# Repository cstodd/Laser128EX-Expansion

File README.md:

# Laser 128EX 1 MB RAM + Clock Expansion

A replacement memory-expansion card for the **Laser 128EX** (and, by the shared connector, the New Laser 128):
**1 MB of battery-backed SRAM** in place of the stock card's 32 DRAMs, plus a **real-time clock** that gives
ProDOS 8 file dates and the time. It plugs into the Laser's internal J13 expansion connector, uses the Laser's
own expansion-RAM interface (`$C0D0–$C0D3`), so the built-in `/RAM5` RAM disk, the firmware and the diagnostics
work unchanged, and the RAM disk survives power-off.

It continues Renée Harke's earlier CPLD + SRAM card for the Laser, which was never finished.

## Status (Nov 2026)
- **Rev 0.2 board: ready to order.** Routed 2-layer, 100 × 90 mm, DRC clean, Gerbers in `hardware/rev02/fab/`.
- **CPLD logic: fitted** (ATF1504AS, 40/64 macrocells); passes its testbench as RTL, fitted equations and decoded
  fuses. The testbench uses strobe timing measured with a scope on a real 128EX (`cpld/rev02/README.md`).
- **ProDOS clock driver: done** (fits in ProDOS's 125-byte clock slot, never disables interrupts), with
  CLOCK.SYSTEM, SET.CLOCK and CARD.TEST on `software/rev02/dist/LASERCLOCK2.po`; emulator-tested.
- **Not yet built.** Next: order boards, assemble, bring up (`docs/bring-up.md`).

## How it works, briefly
The Laser's gate arrays already hold the slinky address register and drive the card with multiplexed DRAM
signals. A CPLD turns those into SRAM addresses and strobes (latching row and column the way DRAM would) for two
512K×8 SRAMs, whose supply and chip enable come from a MAX693A so they keep their contents on a CR2032. J13 has
no spare pins, so the clock (a DS3234 on SPI) is reached **through the RAM data port**: an 8-byte unlock key
written to `$C0D3` switches the CPLD into RTC mode for one transfer. Details: `docs/design-notes.md`.

## Repository
New here (or a fresh Claude session)? Start with `progress.md`, `changelog.md`, `architecture.md` and
`building.md`; `CLAUDE.md` has the working rules.

| Path | What |
|---|---|
| `hardware/rev02/` | **Current board**: KiCad 10 schematic + PCB, `fab/` (Gerbers, drill, BOM, placement), renders, README |
| `cpld/rev02/` | CPLD Verilog, testbench (DS3234 model, measured Laser timing), fitter flow and `.jed` |
| `software/rev02/` | ProDOS clock driver, CLOCK.SYSTEM, SET.CLOCK, CARD.TEST, disk image, emulator tests |
| `docs/ordering.md` | What to order (PCB settings, parts list); open checks in `hardware/rev02/todo.md` |
| `docs/bring-up.md` | Assembly order, programming the CPLD, first power-up and tests |
| `docs/scope-tests.md` | How the J13 timing was measured, with monitor test loops |
| `docs/design-notes.md` | Design decisions and history |
| `docs/laser-expansion-interface.md` | The Laser's expansion RAM interface (from the Technical Reference Manual) |
| `docs/sourcing.md`, `docs/mechanical.md` | Part availability; board outline and clearances |
| `hardware/rev01/`, `cpld/rev01/`, `software/rev01/` | Rev 0.1 (DS3231 on I²C): superseded, kept for reference |
| `tools/` | Scripts that generated / edited the boards and fab outputs |

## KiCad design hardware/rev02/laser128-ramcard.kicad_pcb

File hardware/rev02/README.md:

# Hardware (KiCad) — rev 0.2

Rev 0.2 replaces rev 0.1's DS3231M (I²C, bit-banged through the CPLD) with a **DS3234SN#** (SPI) so the
ProDOS clock driver fits entirely in ProDOS's 125-byte clock slot and never disables interrupts
(`software/rev02`, `cpld/rev02`, `docs/design-notes.md` §10). Everything else (RAM, CPLD, J1, outline,
holes) is unchanged from rev 0.1 (`hardware/rev01`).

Status (rev 0.2): **fully routed, 2 layers, 100 × 90 mm, KiCad 10.** DRC: 0 unconnected, 0 clearance /
silkscreen errors (only "footprint differs from library" notices for footprints carried over from the
KiCad 7 generation). Schematic parity: every pad's net and every footprint/value/field matches; H1/H3 are
board-only mounting holes. J1/H1 geometry re-checked: H1 4.000 mm from the right and bottom edges, J1 pins
15/16 23.000 mm above H1 with J1's centreline through H1. The fab origin (drill/place origin) is the
bottom-left board corner; Gerbers, drill and placement all use it (the 357 drill hits were checked against
the board's pads and vias). Fabrication outputs are in `fab/`. Previews: `render-gerber-top.png` /
`render-gerber-bottom.png` (from the Gerbers with gerbonara), `render-3D-top.png` / `render-3D-bottom.png`
(KiCad 10).

What changed from rev 0.1:
- **U8 DS3234SN#** (SOIC-20W, 300 mil) right of the CPLD, rotated 90°, so CS/SCLK/DIN/DOUT are short.
  DIN (17) and DOUT (19) are joined (3-wire SPI) as `RTC_SDIO`; SCLK on both 18 and 20 (bonded inside);
  N.C. pins 2 and 7–14 and GND 15 to ground (datasheet); VBAT (16) from BT1; 32kHz, INT/SQW, RST open.
  C9 (100 nF) decouples it.
- **R1 1k** CPLD `RTC_DIO` (pin 39) ↔ `RTC_SDIO` (series: limits current if the CPLD and the DS3234 ever drive
  at once). **R2 47k** `RTC_SDIO` → GND: the pull-down the driver relies on to clock in read address 00h.
  Both use the vertical DIN0207 footprint (2.54 mm pitch) to fit beside the CPLD.
- R3–R5 (JTAG pull-ups) and C3 (CPLD decoupling) moved to make room; the strip in front of J1 is kept
  clear for its fan-out.
- CPLD pins 34 / 36 / 39 are now `RTC_CS_n` / `RTC_SCLK` / `RTC_DIO` (were SDA / SCL / MEMRD; MEMRD was
  unused by the logic).
- Board text reads "rev 0.2".
- Strobe timing scoped on a 128EX (Nov 2026): /RWR lags /E1MOE by up to 4.72 ns in accelerated cycles, so the
  CPLD gates SCLK with /RASB as well (already on CPLD pin 2: no board change). See `cpld/rev02/README.md`.

How it was made: `tools/rev02_sch.py` (schematic edit), `tools/rev02_pcb.py` (`prep`: DS3234 footprint and
rev 0.2 nets with stale copper removed; `move`: the placement above; `rip` / `route`: protected incremental
Freerouting passes), then the last two CPLD↔J1 nets (ECAS3_n, ERA8), GND island bridging (U8's ground pins,
U1-10) and moving ECAS3_n / E1MOE_n under U8 on B.Cu were done by hand in KiCad 10, so the scripts no longer
reproduce the board exactly; the `.kicad_pcb` is the source of truth. Fab outputs:
`/usr/bin/python3 tools/export_fab.py rev02`.

Notes on this route:
- Signal tracks 0.2–0.25 mm; GND pours on both layers, stitched with vias.
- J1's socket body goes on the **bottom** side (marked on the bottom silkscreen).
- `laser128-ramcard.pdf` is a plot of the rev 0.2 schematic.

## Project libraries
- `Laser128:Laser128_J1`: J13 mate symbol (pins drawn like the physical socket).
- `Laser128:Laser128_J1_Socket_2x15_P2.54mm_Unumbered`: pins 1–15 down the interior-side row,
  30–16 down the board-edge row. **Not** the stock odd/even 2×15. Print it 1:1 and check against a real socket.
- `Laser128:ATF1504AS-xJx44`: PLCC-44, derived from the stock TQFP-44 ATF1502/1504 symbol
  (PLCC pin = TQFP pin + 6, mod 44). **Verified** against the Atmel-0950 ATF1504AS(L) datasheet tables 16.1/16.2:
  all 32 I/O pins and the dedicated, JTAG and power pins match.

## CPLD pin assignment (ATF1504AS-10JU44, PLCC-44)

| Pin | Signal | Dir | | Pin | Signal | Dir |
|---|---|---|---|---|---|---|
| 1 (GCLR) | /ECAS1 | in | | 21 | COL_LE ('573 LE) | out |
| 2 (GCLK2) | /RASB | in | | 24 | MA18 | out |
| 43 (GCLK1) | /E1MOE | in | | 25 | /RAM_CE → MAX693A CE IN | out |
| 44 (OE1) | /ECAS2 | in | | 26 / 27 | /OE0, /OE1 | out |
| 4, 5 | /ECAS3, /ECAS4 | in | | 28 / 29 | /WE0, /WE1 | out |
| 6 | /RWR | in | | 31 | /BUF_OE ('245 G) | out |
| 8 | ERA8 | in | | 33 / 37 | MA8 (col), MA17 (row) | out |
| 39 | RTC_DIO (via R1 to DS3234 DIN/DOUT) | i/o | | 34 / 36 | RTC_CS_n, RTC_SCLK | out |
| 9 11 12 14 16 17 18 19 | XD0–XD7 | i/o | | 40 / 41 | /PWR_RST (MAX693A), DBG0 (J3) | in, i/o |
| 20 | ROWCLK | out | | 7 13 32 38 | TDI TMS TCK TDO (J2) | jtag |

Power: VCC 3, 15, 23, 35; GND 10, 22, 30, 42.

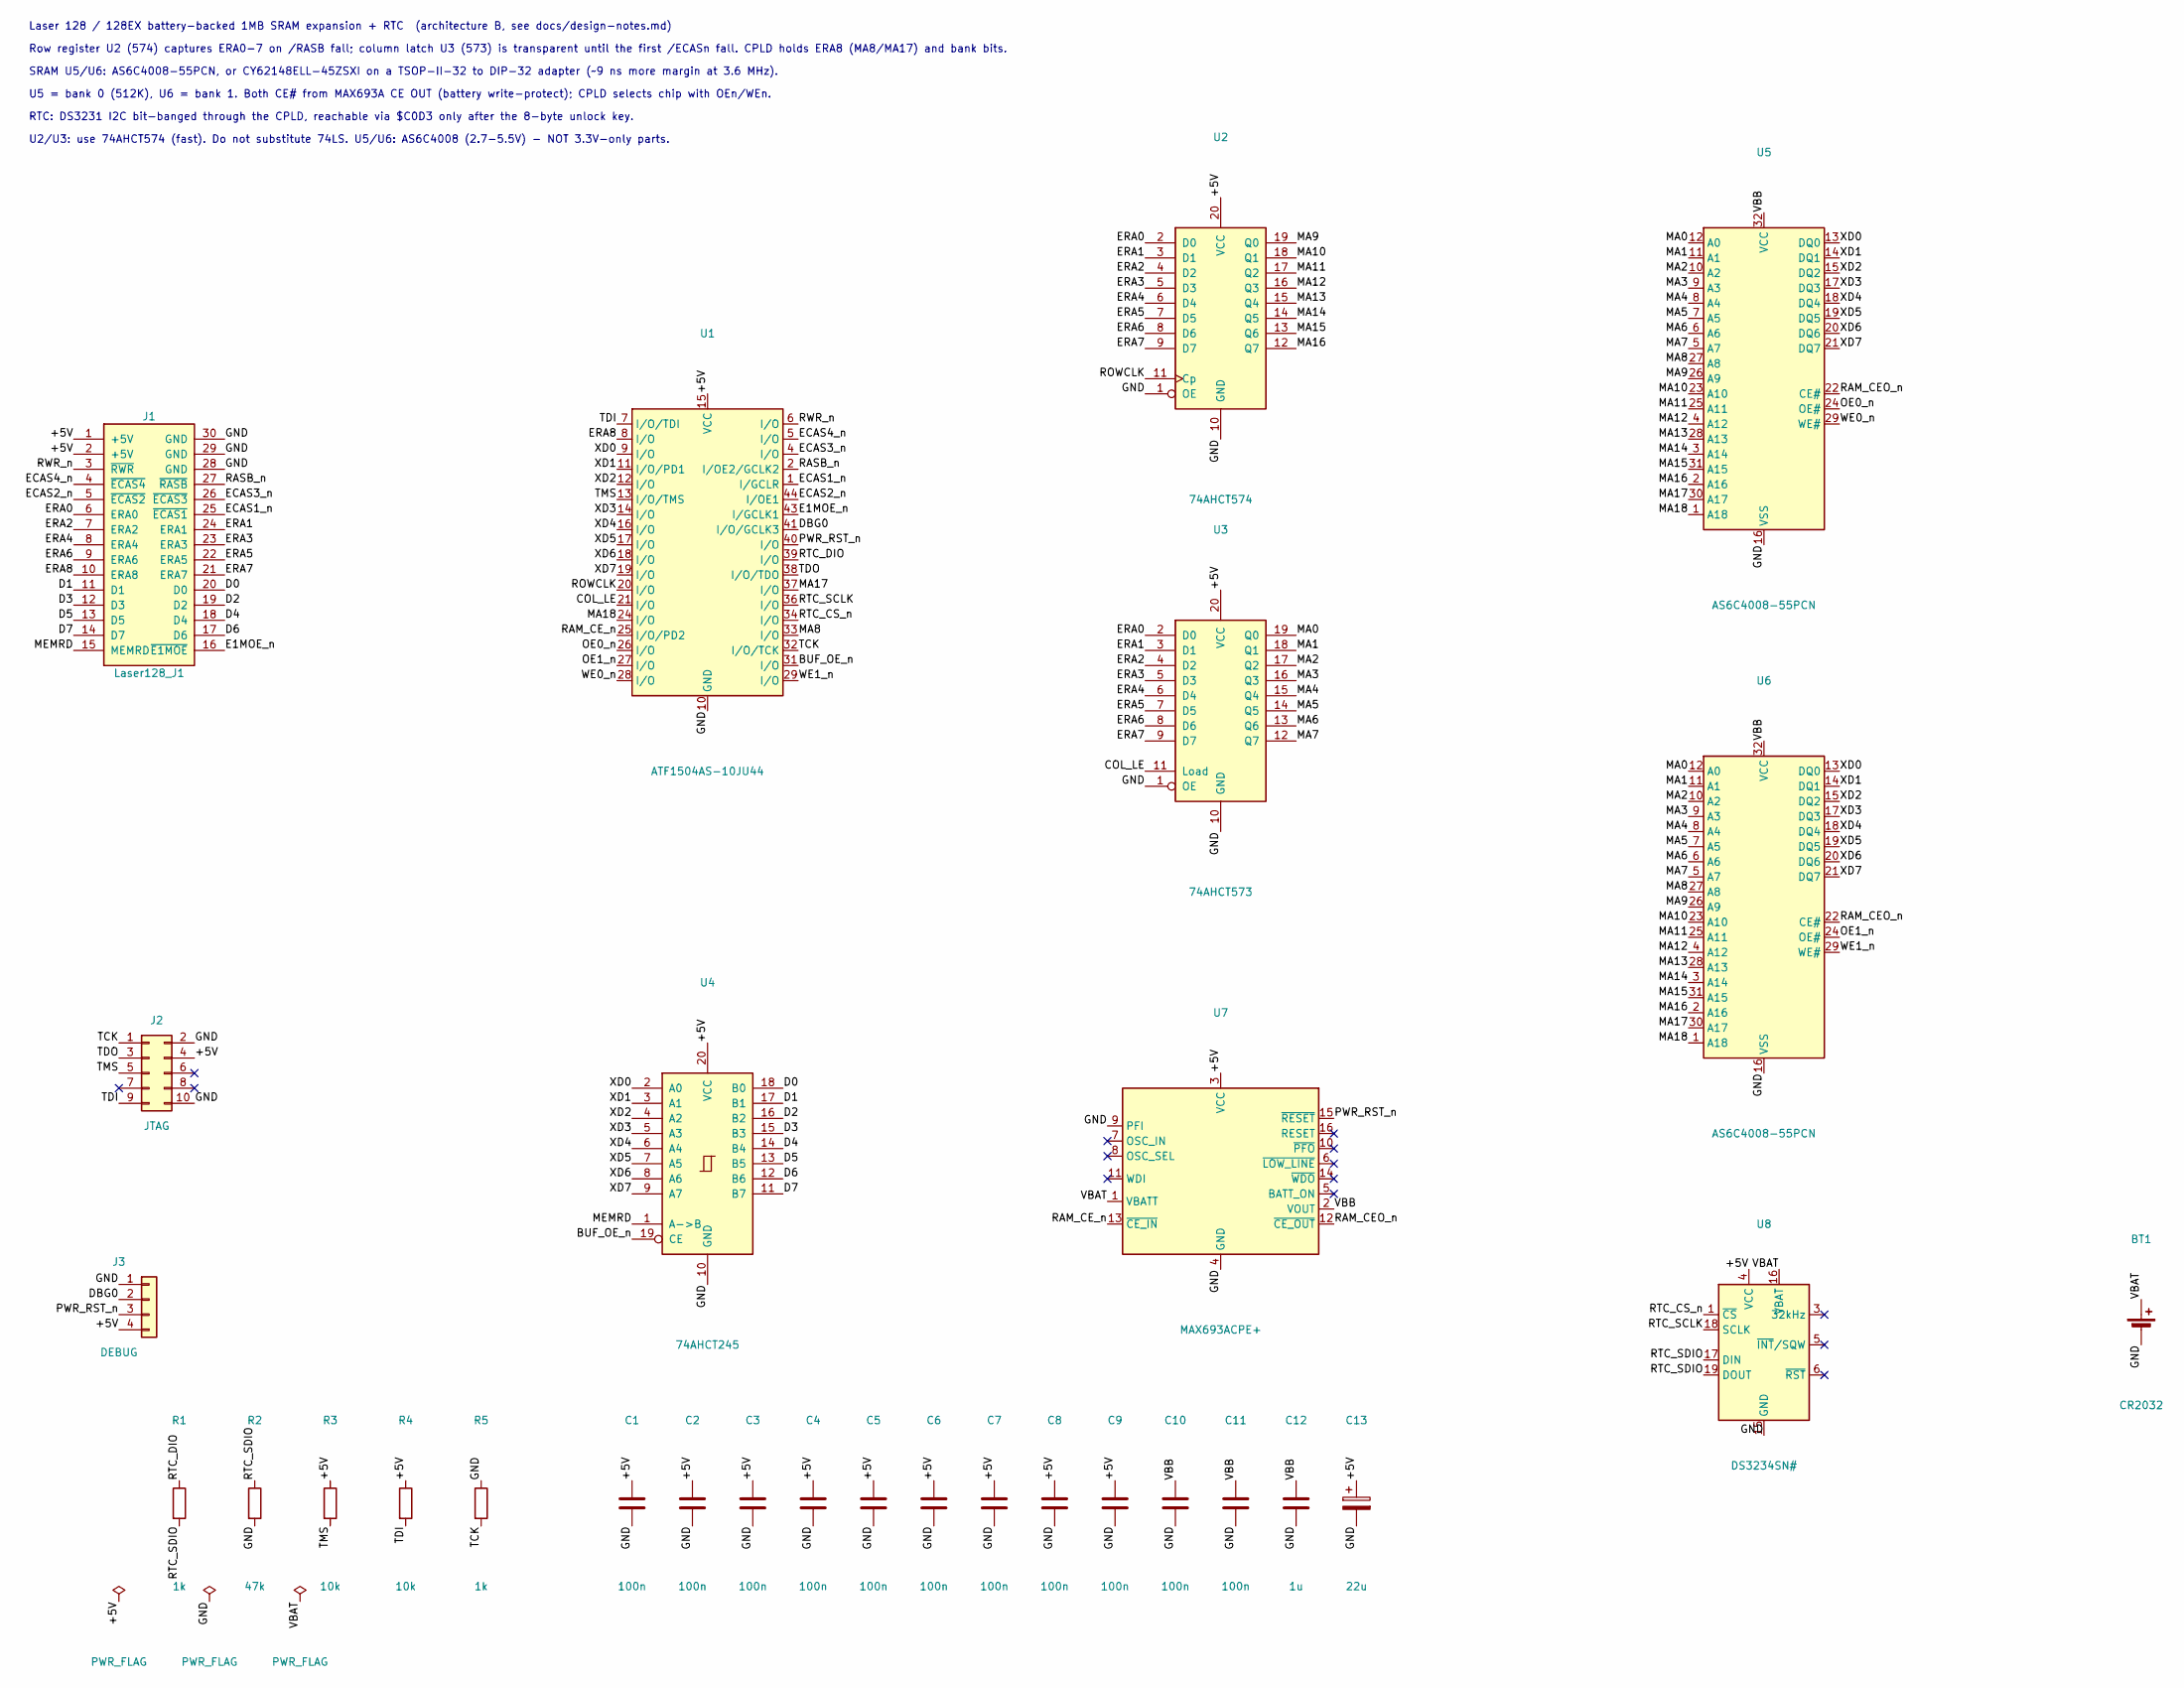
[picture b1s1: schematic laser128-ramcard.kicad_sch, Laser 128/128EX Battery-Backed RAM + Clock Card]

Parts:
BT1: CR2032; BatteryHolder_Keystone_103_1x20mm
C1, C2, C3, C4, C5, C6, C7, C8, C9, C10, C11: 100n; C_Disc_D5.0mm_W2.5mm_P5.00mm
C12: 1u; C_Disc_D5.0mm_W2.5mm_P5.00mm
C13: 22u; CP_Radial_D5.0mm_P2.00mm
J1: Laser128_J1; Laser128_J1_Socket_2x15_P2.54mm_Unumbered
J2: JTAG; IDC-Header_2x05_P2.54mm_Vertical
J3: DEBUG; PinHeader_1x04_P2.54mm_Vertical
R1: 1k; R_Axial_DIN0207_L6.3mm_D2.5mm_P2.54mm_Vertical
R2: 47k; R_Axial_DIN0207_L6.3mm_D2.5mm_P2.54mm_Vertical
R3, R4: 10k; R_Axial_DIN0207_L6.3mm_D2.5mm_P10.16mm_Horizontal
R5: 1k; R_Axial_DIN0207_L6.3mm_D2.5mm_P10.16mm_Horizontal
U1: ATF1504AS-10JU44; PLCC-44_THT-Socket
U2: 74AHCT574; DIP-20_W7.62mm_Socket
U3: 74AHCT573; DIP-20_W7.62mm_Socket
U4: 74AHCT245; DIP-20_W7.62mm_Socket
U5, U6: AS6C4008-55PCN; DIP-32_W15.24mm_Socket
U7: MAX693ACPE+; DIP-16_W7.62mm_Socket
U8: DS3234SN#; SOIC-20W_7.5x12.8mm_P1.27mm

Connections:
/+5V: C1.1, C2.1, C3.1, C4.1, C5.1, C6.1, C7.1, C8.1, C9.1, C13.1, J1.1 (+5V), J1.2 (+5V), J2.4, J3.4, R3.1, R4.1, U1.3 (VCC), U1.15 (VCC), U1.23 (VCC), U1.35 (VCC), U2.20 (VCC), U3.20 (VCC), U4.20 (VCC), U7.3 (VCC), U8.4 (VCC)
/BUF_OE_n: U1.31 (I/O), U4.19 (CE)
/COL_LE: U1.21 (I/O), U3.11 (Load)
/D0: J1.20 (D0), U4.18 (B0)
/D1: J1.11 (D1), U4.17 (B1)
/D2: J1.19 (D2), U4.16 (B2)
/D3: J1.12 (D3), U4.15 (B3)
/D4: J1.18 (D4), U4.14 (B4)
/D5: J1.13 (D5), U4.13 (B5)
/D6: J1.17 (D6), U4.12 (B6)
/D7: J1.14 (D7), U4.11 (B7)
/DBG0: J3.2, U1.41 (I/O/GCLK3)
/E1MOE_n: J1.16 (~E1MOE), U1.43 (I/GCLK1)
/ECAS1_n: J1.25 (~ECAS1), U1.1 (I/GCLR)
/ECAS2_n: J1.5 (~ECAS2), U1.44 (I/OE1)
/ECAS3_n: J1.26 (~ECAS3), U1.4 (I/O)
/ECAS4_n: J1.4 (~ECAS4), U1.5 (I/O)
/ERA0: J1.6 (ERA0), U2.2 (D0), U3.2 (D0)
/ERA1: J1.24 (ERA1), U2.3 (D1), U3.3 (D1)
/ERA2: J1.7 (ERA2), U2.4 (D2), U3.4 (D2)
/ERA3: J1.23 (ERA3), U2.5 (D3), U3.5 (D3)
/ERA4: J1.8 (ERA4), U2.6 (D4), U3.6 (D4)
/ERA5: J1.22 (ERA5), U2.7 (D5), U3.7 (D5)
/ERA6: J1.9 (ERA6), U2.8 (D6), U3.8 (D6)
/ERA7: J1.21 (ERA7), U2.9 (D7), U3.9 (D7)
/ERA8: J1.10 (ERA8), U1.8 (I/O)
/GND: BT1.2 (-), C1.2, C2.2, C3.2, C4.2, C5.2, C6.2, C7.2, C8.2, C9.2, C10.2, C11.2, C12.2, C13.2, J1.28 (GND), J1.29 (GND), J1.30 (GND), J2.2, J2.10, J3.1, R2.2, R5.1, U1.10 (GND), U1.22 (GND), U1.30 (GND), U1.42 (GND), U2.1 (OE), U2.10 (GND), U3.1 (OE), U3.10 (GND), U4.10 (GND), U5.16 (VSS), U6.16 (VSS), U7.4 (GND), U7.9 (PFI), U8.2 (GND), U8.7 (GND), U8.8 (GND), U8.9 (GND), U8.10 (GND), U8.11 (GND), U8.12 (GND), U8.13 (GND), U8.14 (GND), U8.15 (GND); also elsewhere on the board
/MA0: U3.19 (Q0), U5.12 (A0), U6.12 (A0)
/MA1: U3.18 (Q1), U5.11 (A1), U6.11 (A1)
/MA2: U3.17 (Q2), U5.10 (A2), U6.10 (A2)
/MA3: U3.16 (Q3), U5.9 (A3), U6.9 (A3)
/MA4: U3.15 (Q4), U5.8 (A4), U6.8 (A4)
/MA5: U3.14 (Q5), U5.7 (A5), U6.7 (A5)
/MA6: U3.13 (Q6), U5.6 (A6), U6.6 (A6)
/MA7: U3.12 (Q7), U5.5 (A7), U6.5 (A7)
/MA8: U1.33 (I/O), U5.27 (A8), U6.27 (A8)
/MA9: U2.19 (Q0), U5.26 (A9), U6.26 (A9)
/MA10: U2.18 (Q1), U5.23 (A10), U6.23 (A10)
/MA11: U2.17 (Q2), U5.25 (A11), U6.25 (A11)
/MA12: U2.16 (Q3), U5.4 (A12), U6.4 (A12)
/MA13: U2.15 (Q4), U5.28 (A13), U6.28 (A13)
/MA14: U2.14 (Q5), U5.3 (A14), U6.3 (A14)
/MA15: U2.13 (Q6), U5.31 (A15), U6.31 (A15)
/MA16: U2.12 (Q7), U5.2 (A16), U6.2 (A16)
/MA17: U1.37 (I/O), U5.30 (A17), U6.30 (A17)
/MA18: U1.24 (I/O), U5.1 (A18), U6.1 (A18)
/MEMRD: J1.15 (MEMRD), U4.1 (A->B)
/OE0_n: U1.26 (I/O), U5.24 (OE#)
/OE1_n: U1.27 (I/O), U6.24 (OE#)
/PWR_RST_n: J3.3, U1.40 (I/O), U7.15 (~RESET)
/RAM_CEO_n: U5.22 (CE#), U6.22 (CE#), U7.12 (~CE_OUT)
/RAM_CE_n: U1.25 (I/O/PD2), U7.13 (~CE_IN)
/RASB_n: J1.27 (~RASB), U1.2 (I/OE2/GCLK2)
/ROWCLK: U1.20 (I/O), U2.11 (Cp)
/RTC_CS_n: U1.34 (I/O), U8.1 (~CS)
/RTC_DIO: R1.1, U1.39 (I/O)
/RTC_SCLK: U1.36 (I/O), U8.18 (SCLK), U8.20 (SCLK)
/RTC_SDIO: R1.2, R2.1, U8.17 (DIN), U8.19 (DOUT)
/RWR_n: J1.3 (~RWR), U1.6 (I/O)
/TCK: J2.1, R5.2, U1.32 (I/O/TCK)
/TDI: J2.9, R4.2, U1.7 (I/O/TDI)
/TDO: J2.3, U1.38 (I/O/TDO)
/TMS: J2.5, R3.2, U1.13 (I/O/TMS)
/VBAT: BT1.1 (+), U7.1 (VBATT), U8.16 (VBAT)
/VBB: C10.1, C11.1, C12.1, U5.32 (VCC), U6.32 (VCC), U7.2 (VOUT)
/WE0_n: U1.28 (I/O), U5.29 (WE#)
/WE1_n: U1.29 (I/O), U6.29 (WE#)
/XD0: U1.9 (I/O), U4.2 (A0), U5.13 (DQ0), U6.13 (DQ0)
/XD1: U1.11 (I/O/PD1), U4.3 (A1), U5.14 (DQ1), U6.14 (DQ1)
/XD2: U1.12 (I/O), U4.4 (A2), U5.15 (DQ2), U6.15 (DQ2)
/XD3: U1.14 (I/O), U4.5 (A3), U5.17 (DQ3), U6.17 (DQ3)
/XD4: U1.16 (I/O), U4.6 (A4), U5.18 (DQ4), U6.18 (DQ4)
/XD5: U1.17 (I/O), U4.7 (A5), U5.19 (DQ5), U6.19 (DQ5)
/XD6: U1.18 (I/O), U4.8 (A6), U5.20 (DQ6), U6.20 (DQ6)
/XD7: U1.19 (I/O), U4.9 (A7), U5.21 (DQ7), U6.21 (DQ7)

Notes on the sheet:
Laser 128 / 128EX battery-backed 1MB SRAM expansion + RTC (architecture B, see docs/design-notes.md)
Row register U2 (574) captures ERA0-7 on /RASB fall; column latch U3 (573) is transparent until the first /ECASn fall. CPLD holds ERA8 (MA8/MA17) and bank bits.
SRAM U5/U6: AS6C4008-55PCN, or CY62148ELL-45ZSXI on a TSOP-II-32 to DIP-32 adapter (~9 ns more margin at 3.6 MHz).
U5 = bank 0 (512K), U6 = bank 1. Both CE# from MAX693A CE OUT (battery write-protect); CPLD selects chip with OEn/WEn.
RTC: DS3231 I2C bit-banged through the CPLD, reachable via $C0D3 only after the 8-byte unlock key.
U2/U3: use 74AHCT574 (fast). Do not substitute 74LS. U5/U6: AS6C4008 (2.7-5.5V) - NOT 3.3V-only parts.

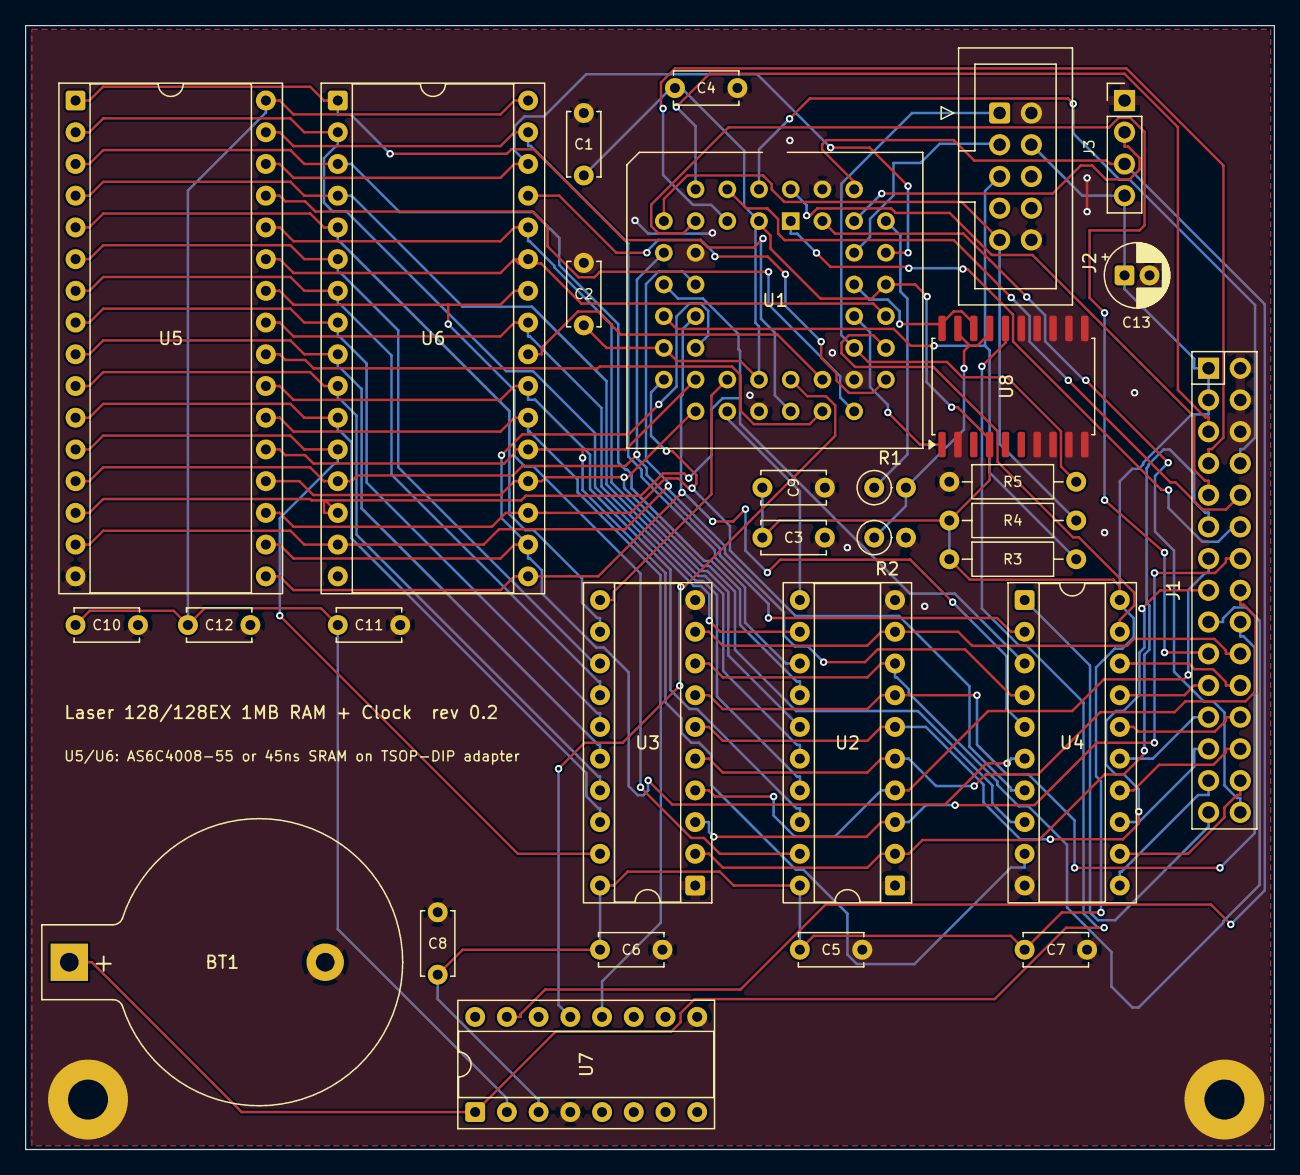
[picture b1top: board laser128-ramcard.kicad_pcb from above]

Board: 2 copper layers, 100.0 x 90.0 mm, 32 parts (0 on the bottom side), 75 nets.

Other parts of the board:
H1: M3, Laser standoff; MountingHole_3.2mm_M3_Pad
H3: M3 standoff; MountingHole_3.2mm_M3_Pad

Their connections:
/GND: H1.1, H3.1; also elsewhere on the board

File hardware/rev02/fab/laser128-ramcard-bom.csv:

Comment,Designator,Footprint,Qty
CR2032,BT1,BatteryHolder_Keystone_103_1x20mm,1
1u,C12,C_Disc_D5.0mm_W2.5mm_P5.00mm,1
22u,C13,CP_Radial_D5.0mm_P2.00mm,1
100n,"C1,C2,C3,C4,C5,C6,C7,C8,C9,C10,C11",C_Disc_D5.0mm_W2.5mm_P5.00mm,11
Laser128_J1,J1,Laser128_J1_Socket_2x15_P2.54mm_Unumbered,1
JTAG,J2,IDC-Header_2x05_P2.54mm_Vertical,1
DEBUG,J3,PinHeader_1x04_P2.54mm_Vertical,1
1k,R1,R_Axial_DIN0207_L6.3mm_D2.5mm_P2.54mm_Vertical,1
47k,R2,R_Axial_DIN0207_L6.3mm_D2.5mm_P2.54mm_Vertical,1
10k,"R3,R4",R_Axial_DIN0207_L6.3mm_D2.5mm_P10.16mm_Horizontal,2
1k,R5,R_Axial_DIN0207_L6.3mm_D2.5mm_P10.16mm_Horizontal,1
ATF1504AS-10JU44,U1,PLCC-44_THT-Socket,1
74AHCT574,U2,DIP-20_W7.62mm_Socket,1
74AHCT573,U3,DIP-20_W7.62mm_Socket,1
74AHCT245,U4,DIP-20_W7.62mm_Socket,1
AS6C4008-55PCN,"U5,U6",DIP-32_W15.24mm_Socket,2
MAX693ACPE+,U7,DIP-16_W7.62mm_Socket,1
DS3234SN#,U8,SOIC-20W_7.5x12.8mm_P1.27mm,1

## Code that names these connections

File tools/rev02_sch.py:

#!/usr/bin/env python3
"""Rev 0.2 schematic edit (hardware/rev02): DS3231M (I2C) -> DS3234SN# (SPI). Text-level edits of the
KiCad schematic (KiCad has no schematic Python API). Run once on the copy of rev 0.1; checked by ERC + netlist.
  U8: Timer_RTC:DS3231M -> Laser128:DS3234, SOIC-20W; labels/no-connects re-placed at the new pin positions.
  R1: 4.7k pull-up -> 1k series, RTC_DIO (CPLD pin 39) to RTC_SDIO (DS3234 DIN+DOUT).
  R2: 4.7k pull-up -> 47k pull-down, RTC_SDIO to GND.
  U1 (CPLD): pin 34 SDA -> RTC_CS_n, pin 36 SCL -> RTC_SCLK, pin 39 MEMRD -> RTC_DIO (MEMRD stays on J1 + U4).
"""
import os, re, sys, uuid
ROOT = os.path.dirname(os.path.dirname(os.path.abspath(__file__)))
HW = os.path.join(ROOT, 'hardware', 'rev02')
SCH = os.path.join(HW, 'laser128-ramcard.kicad_sch')
LIB = os.path.join(HW, 'lib', 'Laser128.kicad_sym')
U8X, U8Y = 317.5, 236.22

def u(): return str(uuid.uuid4())
def pin(kind, x, y, ang, name, num, hide=False):
    return ('        (pin %s line\n          (at %s %s %d)\n          (length 2.54)%s\n'
            '          (name "%s"\n            (effects\n              (font\n                (size 1.27 1.27))))\n'
            '          (number "%s"\n            (effects\n              (font\n                (size 1.27 1.27)))))\n'
            % (kind, x, y, ang, ' hide' if hide else '', name, num))

# DS3234 symbol (KiCad Y up). Pin ends: left x=-10.16, right x=10.16, top y=12.7, bottom y=-15.24.
PINS = [('input', -10.16, 5.08, 0, '~{CS}', '1', False), ('input', -10.16, 2.54, 0, 'SCLK', '18', False),
        ('input', -10.16, 2.54, 0, 'SCLK', '20', True), ('input', -10.16, -2.54, 0, 'DIN', '17', False),
        ('tri_state', -10.16, -5.08, 0, 'DOUT', '19', False),
        ('power_in', -2.54, 12.7, 270, 'VCC', '4', False), ('power_in', 2.54, 12.7, 270, 'VBAT', '16', False),
        ('output', 10.16, 5.08, 180, '32kHz', '3', False), ('open_collector', 10.16, 0, 180, '~{INT}/SQW', '5', False),
        ('bidirectional', 10.16, -5.08, 180, '~{RST}', '6', False), ('power_in', 0, -15.24, 90, 'GND', '15', False)]
PINS += [('passive', 0, -15.24, 90, 'GND', n, True) for n in ('2', '7', '8', '9', '10', '11', '12', '13', '14')]

def symbol(name, in_sch):
    s = '    (symbol "%s"\n      (in_bom yes)\n      (on_board yes)\n' % name
    for k, v, at, hide in [('Reference', 'U', '-7.62 11.43 0', False), ('Value', 'DS3234', '1.27 -13.97 0', False),
                           ('Footprint', 'Package_SO:SOIC-20W_7.5x12.8mm_P1.27mm', '0 -19.05 0', True),
                           ('Datasheet', 'https://www.analog.com/media/en/technical-documentation/data-sheets/DS3234.pdf', '0 -21.59 0', True),
                           ('ki_description', 'Extremely accurate SPI RTC/TCXO/crystal + 256 B SRAM, SO-20W. N.C. pins 2, 7-14 must be grounded (stacked on GND here)', '0 0 0', True),
                           ('ki_fp_filters', 'SOIC*7.5x12.8mm*P1.27mm*', '0 0 0', True)]:
        s += ('      (property "%s" "%s"\n        (at %s)\n        (effects\n          (font\n            (size 1.27 1.27))%s))\n'
              % (k, v, at, ' hide' if hide else ''))
    base = name.split(':')[-1]
    s += ('      (symbol "%s_0_1"\n        (rectangle\n          (start -7.62 10.16)\n          (end 7.62 -12.7)\n'
          '          (stroke\n            (width 0.254)\n            (type default))\n          (fill\n            (type background))))\n' % base)
    s += '      (symbol "%s_1_1"\n' % base + ''.join(pin(*p) for p in PINS) + '      ))\n'
    return s

def abs_pin(num):
    p = [p for p in PINS if p[5] == num][0]
    return round(U8X + p[1], 2), round(U8Y - p[2], 2)

def main():
    t = open(SCH).read()
    # --- library symbol: replace the embedded DS3231M with DS3234
    i = t.index('    (symbol "Timer_RTC:DS3231M"'); j = i
    depth = 0
    while True:
        c = t[j]; depth += c == '('; depth -= c == ')'; j += 1
        if depth == 0: break
    t = t[:i] + symbol('Laser128:DS3234', True).rstrip('\n') + t[j:]
    # --- labels: rename by (old name, x, y)
    def relabel(old, new, x, y):
        nonlocal t
        pat = re.compile(r'\(label "%s"\s*\(at %s %s ' % (re.escape(old), re.escape(fmt(x)), re.escape(fmt(y))))
        m = pat.search(t); assert m, (old, x, y)
        t = t[:m.start()] + '(label "%s"' % new + t[m.start() + len('(label "%s"' % old):]
    def fmt(v): return ('%g' % v)
    def block_at(kind, name, x, y):
        pat = re.compile(r'\n\s*\(%s\s+%s\s*\(at %s %s[ )]' % (kind, ('"%s"' % re.escape(name)) if name else '', re.escape(fmt(x)), re.escape(fmt(y))))
        m = pat.search(t); assert m, (kind, name, x, y)
        k = m.start() + 1
        while t[k] != '(': k += 1
        d = 0; e = k
        while True:
            c = t[e]; d += c == '('; d -= c == ')'; e += 1
            if d == 0: break
        return m.start(), e
    def delete(kind, name, x, y):
        nonlocal t
        s, e = block_at(kind, name, x, y); t = t[:s] + t[e:]
    def add_label(name, x, y, ang, template):
        nonlocal t
        b = re.sub(r'\(at [-\d.]+ [-\d.]+ \d+\)', '(at %s %s %d)' % (fmt(x), fmt(y), ang), template, 1)
        b = re.sub(r'\(label "[^"]*"', '(label "%s"' % name, b, 1)
        b = re.sub(r'\(uuid "[^"]*"\)', '(uuid "%s")' % u(), b)
        b = re.sub(r'\(justify (left|right)\)', '(justify %s)' % ('right' if ang == 180 else 'left'), b)
        t = t.replace('\n  (sheet_instances', b + '\n  (sheet_instances', 1) if '(sheet_instances' in t else t[:t.rindex(')')] + b + '\n)'
    def add_nc(x, y):
        nonlocal t
        b = '\n  (no_connect\n    (at %s %s)\n    (uuid "%s"))' % (fmt(x), fmt(y), u())
        t = t.replace('\n  (sheet_instances', b + '\n  (sheet_instances', 1) if '(sheet_instances' in t else t[:t.rindex(')')] + b + '\n)'
    s, e = block_at('label', 'SDA', 304.8, 233.68); template = t[s:e]
    # CPLD pins
    relabel('SDA', 'RTC_CS_n', 154.94, 114.3); relabel('SCL', 'RTC_SCLK', 154.94, 111.76); relabel('MEMRD', 'RTC_DIO', 154.94, 104.14)
    # R1, R2
    relabel('+5V', 'RTC_DIO', 50.8, 259.08); relabel('SDA', 'RTC_SDIO', 50.8, 266.7)
    relabel('+5V', 'RTC_SDIO', 63.5, 259.08); relabel('SCL', 'GND', 63.5, 266.7)
    # U8: old labels / no-connects out
    for n, x, y in [('+5V', 314.96, 226.06), ('VBAT', 317.5, 226.06), ('GND', 317.5, 246.38), ('SDA', 304.8, 233.68), ('SCL', 304.8, 231.14)]:
        delete('label', n, x, y)
    for x, y in [(330.2, 231.14), (330.2, 238.76), (304.8, 241.3)]:
        delete('no_connect', None, x, y)
    for name, num, ang in [('RTC_CS_n', '1', 180), ('RTC_SCLK', '18', 180), ('RTC_SDIO', '17', 180), ('RTC_SDIO', '19', 180),
                           ('+5V', '4', 0), ('VBAT', '16', 0), ('GND', '15', 0)]:
        add_label(name, *abs_pin(num), ang, template)
    for num in ('3', '5', '6'):
        add_nc(*abs_pin(num))
    # U8 instance
    i = t.index('(lib_id "Timer_RTC:DS3231M"'); s = t.rindex('\n  (symbol', 0, i)
    d = 0; e = t.index('(', s)
    while True:
        c = t[e]; d += c == '('; d -= c == ')'; e += 1
        if d == 0: break
    blk = t[s:e]
    blk = blk.replace('(lib_id "Timer_RTC:DS3231M"', '(lib_id "Laser128:DS3234"')
    blk = blk.replace('"DS3231M+"', '"DS3234SN#"').replace('Package_SO:SOIC-16W_7.5x10.3mm_P1.27mm', 'Package_SO:SOIC-20W_7.5x12.8mm_P1.27mm')
    blk = re.sub(r'\(property "Datasheet" "[^"]*"', '(property "Datasheet" "https://www.analog.com/media/en/technical-documentation/data-sheets/DS3234.pdf"', blk)
    blk = re.sub(r'\n\s*\(pin "\d+"\s*\(uuid "[^"]*"\)\)', '', blk)
    pins = ''.join('\n    (pin "%d"\n      (uuid "%s"))' % (n, u()) for n in range(1, 21))
    k = blk.index('\n    (instances') if '\n    (instances' in blk else blk.rindex(')')
    blk = blk[:k] + pins + blk[k:]
    t = t[:s] + blk + t[e:]
    # R values
    for ref, val in (('R1', '1k'), ('R2', '47k')):
        i = t.index('(property "Reference" "%s"' % ref); s = t.rindex('\n  (symbol', 0, i)
        e = t.index('(property "Value" "4.7k"', s); assert e < i + 2000
        t = t[:e] + '(property "Value" "%s"' % val + t[e + len('(property "Value" "4.7k"'):]
    # R1/R2 use the vertical DIN0207 footprint so the DS3234 cluster fits beside the CPLD (rev02_pcb.py move)
    for ref in ('R1', 'R2'):
        i = t.index('(property "Reference" "%s"' % ref); s = t.rindex('\n  (symbol', 0, i)
        h = 'Resistor_THT:R_Axial_DIN0207_L6.3mm_D2.5mm_P10.16mm_Horizontal'
        e = t.index(h, s); assert e < i + 2000
        t = t[:e] + 'Resistor_THT:R_Axial_DIN0207_L6.3mm_D2.5mm_P2.54mm_Vertical' + t[e + len(h):]
    open(SCH, 'w').write(t)
    # project library
    L = open(LIB).read()
    if '(symbol "DS3234"' not in L:
        L = L[:L.rindex(')')] + symbol('DS3234', False) + ')\n'
        open(LIB, 'w').write(L)
    print('rev02 schematic edited')

if __name__ == '__main__':
    main()

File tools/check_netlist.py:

#!/usr/bin/env python3
"""Electrical sanity checks on the exported KiCad netlist (stands in for ERC, which the
KiCad 7 CLI lacks).  Usage: check_netlist.py <netlist.net>

Checks:
  * no single-pin nets except the explicitly allowed no-connects
  * at most one driver (output/power_out) per net; tri-state outputs only on known buses
  * every power_in pin sits on a supply net
  * J1 matches the Tech Ref Manual J13 table (entered independently below)
  * every SRAM address/data/control line reaches both SRAMs and has exactly one source
"""
import os
import sys

sys.path.insert(0, os.path.dirname(__file__))
from sexp import parse, find, find1  # noqa: E402

ALLOWED_NC = {('J2', '6'), ('J2', '7'), ('J2', '8'), ('U8', '1'), ('U8', '3'), ('U8', '4')} | \
             {('U7', p) for p in ('5', '6', '7', '8', '10', '11', '14', '16')}
SUPPLIES = {'+5V', 'GND', 'VBB', 'VBAT'}
TRISTATE_BUSES = {'XD%d' % i for i in range(8)} | {'D%d' % i for i in range(8)} | \
                 {'MA%d' % i for i in range(19)}

# Independent re-entry of LASER 128EX J13 (Tech Ref Manual D-102), pin: net
J13 = """1 +5V 2 +5V 3 RWR_n 4 ECAS4_n 5 ECAS2_n 6 ERA0 7 ERA2 8 ERA4 9 ERA6 10 ERA8
11 D1 12 D3 13 D5 14 D7 15 MEMRD 16 E1MOE_n 17 D6 18 D4 19 D2 20 D0 21 ERA7 22 ERA5
23 ERA3 24 ERA1 25 ECAS1_n 26 ECAS3_n 27 RASB_n 28 GND 29 GND 30 GND""".split()
J13 = dict(zip(J13[0::2], J13[1::2]))


def main(path):
    t = parse(open(path).read())
    nets = {}
    pinnet = {}
    for n in find(find1(t, 'nets'), 'net'):
        name = find1(n, 'name')[1].lstrip('/')
        nodes = []
        for x in find(n, 'node'):
            ref, pin = find1(x, 'ref')[1], find1(x, 'pin')[1]
            ptype = find1(x, 'pintype')[1] if find1(x, 'pintype') else 'unspecified'
            nodes.append((ref, pin, ptype))
            pinnet[(ref, pin)] = name
        nets[name] = nodes
    err = []

    for name, nodes in nets.items():
        if len(nodes) < 2 and (nodes[0][0], nodes[0][1]) not in ALLOWED_NC:
            err.append('single-pin net %s %s' % (name, nodes))
        drivers = [x for x in nodes if x[2].split('+')[0] in ('output', 'power_out')]
        if len(drivers) > 1:
            err.append('multiple drivers on %s: %s' % (name, drivers))
        tri = [x for x in nodes if x[2].startswith('tri_state')]
        if tri and name not in TRISTATE_BUSES:
            err.append('tri-state pin on non-bus net %s: %s' % (name, tri))
        for x in nodes:
            if x[2].startswith('power_in') and name not in SUPPLIES:
                err.append('power_in pin %s.%s on non-supply net %s' % (x[0], x[1], name))

    for pin, want in J13.items():
        got = pinnet.get(('J1', pin))
        if got != want:
            err.append('J1 pin %s is %s, manual says %s' % (pin, got, want))

    for i in range(19):
        n = 'MA%d' % i
        refs = sorted({r for r, p, _ in nets.get(n, [])})
        if not {'U5', 'U6'} <= set(refs):
            err.append('%s does not reach both SRAMs: %s' % (n, refs))
        src = [x for x in nets.get(n, []) if x[0] in ('U1', 'U2', 'U3')]
        if len(src) != 1:
            err.append('%s should have exactly one source (U1/U2/U3), has %s' % (n, src))
    for i in range(8):
        refs = {r for r, p, _ in nets.get('XD%d' % i, [])}
        if refs != {'U1', 'U4', 'U5', 'U6'}:
            err.append('XD%d connects %s' % (i, sorted(refs)))
        refs = {r for r, p, _ in nets.get('D%d' % i, [])}
        if refs != {'J1', 'U4'}:
            err.append('D%d connects %s' % (i, sorted(refs)))
    # SRAM supply must be battery-backed; chip enable must come through the DS1210
    for ref in ('U5', 'U6'):
        if pinnet.get((ref, '32')) != 'VBB':
            err.append('%s VCC not on VBB' % ref)
        if pinnet.get((ref, '22')) != 'RAM_CEO_n':
            err.append('%s CE# not from supervisor CE OUT' % ref)
    if pinnet.get(('U7', '12')) != 'RAM_CEO_n' or pinnet.get(('U7', '13')) != 'RAM_CE_n' or \
            pinnet.get(('U7', '2')) != 'VBB' or pinnet.get(('U7', '1')) != 'VBAT':
        err.append('U7 (MAX693A) CE/VOUT/VBATT wiring wrong')
    if pinnet.get(('U1', '40')) != 'PWR_RST_n' or pinnet.get(('U7', '15')) != 'PWR_RST_n':
        err.append('power-on reset not wired U7.15 -> U1.40')

    print('%d nets, %d pins checked' % (len(nets), len(pinnet)))
    if err:
        print('\n'.join('ERROR: ' + e for e in err))
        return 1
    print('OK: no errors')
    return 0


if __name__ == '__main__':
    sys.exit(main(sys.argv[1]))
